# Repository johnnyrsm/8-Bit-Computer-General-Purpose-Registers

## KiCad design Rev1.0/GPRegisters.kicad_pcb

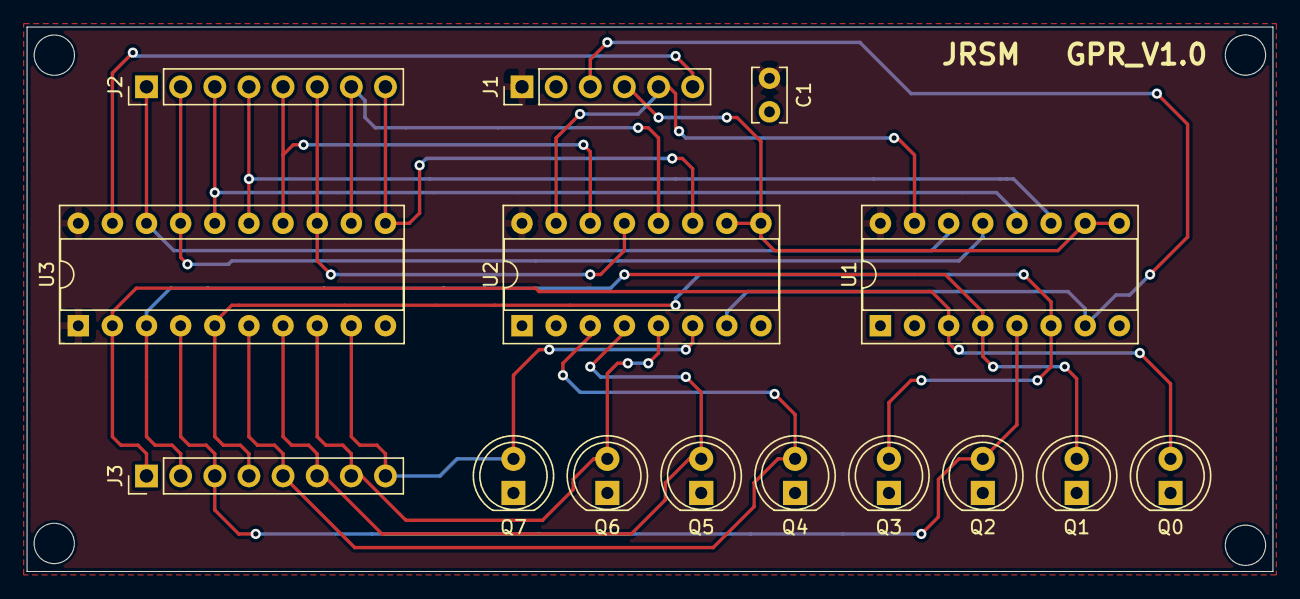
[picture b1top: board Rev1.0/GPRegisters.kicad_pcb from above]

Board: 2 copper layers, 92.7 x 40.5 mm, 15 parts (0 on the bottom side), 22 nets.

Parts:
C1: 1uF; C_Rect_L4.0mm_W2.5mm_P2.50mm
J1: Conn_01x06; Pin_Header_Straight_1x06_Pitch2.54mm
J2, J3: Conn_01x08; Pin_Header_Straight_1x08_Pitch2.54mm
Q0, Q1, Q2, Q3, Q4, Q5, Q6, Q7: LED; LED_D5.0mm
U1, U2: 74LS173; DIP-16_W7.62mm_Socket
U3: 74LS245; DIP-20_W7.62mm_Socket

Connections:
/CLK: J1.3, U1.7, U2.7
/CLR: J1.5, U1.15, U2.15
/D0: J2.1, U1.14, U3.18
/D1: J2.2, U1.13, U3.17
/D2: J2.3, U1.12, U3.16
/D3: J2.4, U1.11, U3.15
/D4: J2.5, U2.14, U3.14
/D5: J2.6, U2.13, U3.13
/D6: J2.7, U2.12, U3.12
/D7: J2.8, U2.11, U3.11
/Q0: J3.1, Q0.2, U1.3, U3.2
/Q1: J3.2, Q1.2, U1.4, U3.3
/Q2: J3.3, Q2.2, U1.5, U3.4
/Q3: J3.4, Q3.2, U1.6, U3.5
/Q4: J3.5, Q4.2, U2.3, U3.6
/Q5: J3.6, Q5.2, U2.4, U3.7
/Q6: J3.7, Q6.2, U2.5, U3.8
/Q7: J3.8, Q7.2, U2.6, U3.9
/~EN: J1.6, U3.19
/~LOAD: J1.4, U1.9, U1.10, U2.9, U2.10
GND: C1.2, J1.2, Q0.1, Q1.1, Q2.1, Q3.1, Q4.1, Q5.1, Q6.1, Q7.1, U1.1, U1.2, U1.8, U2.1, U2.2, U2.8, U3.10
VCC: C1.1, J1.1, U1.16, U2.16, U3.1, U3.20

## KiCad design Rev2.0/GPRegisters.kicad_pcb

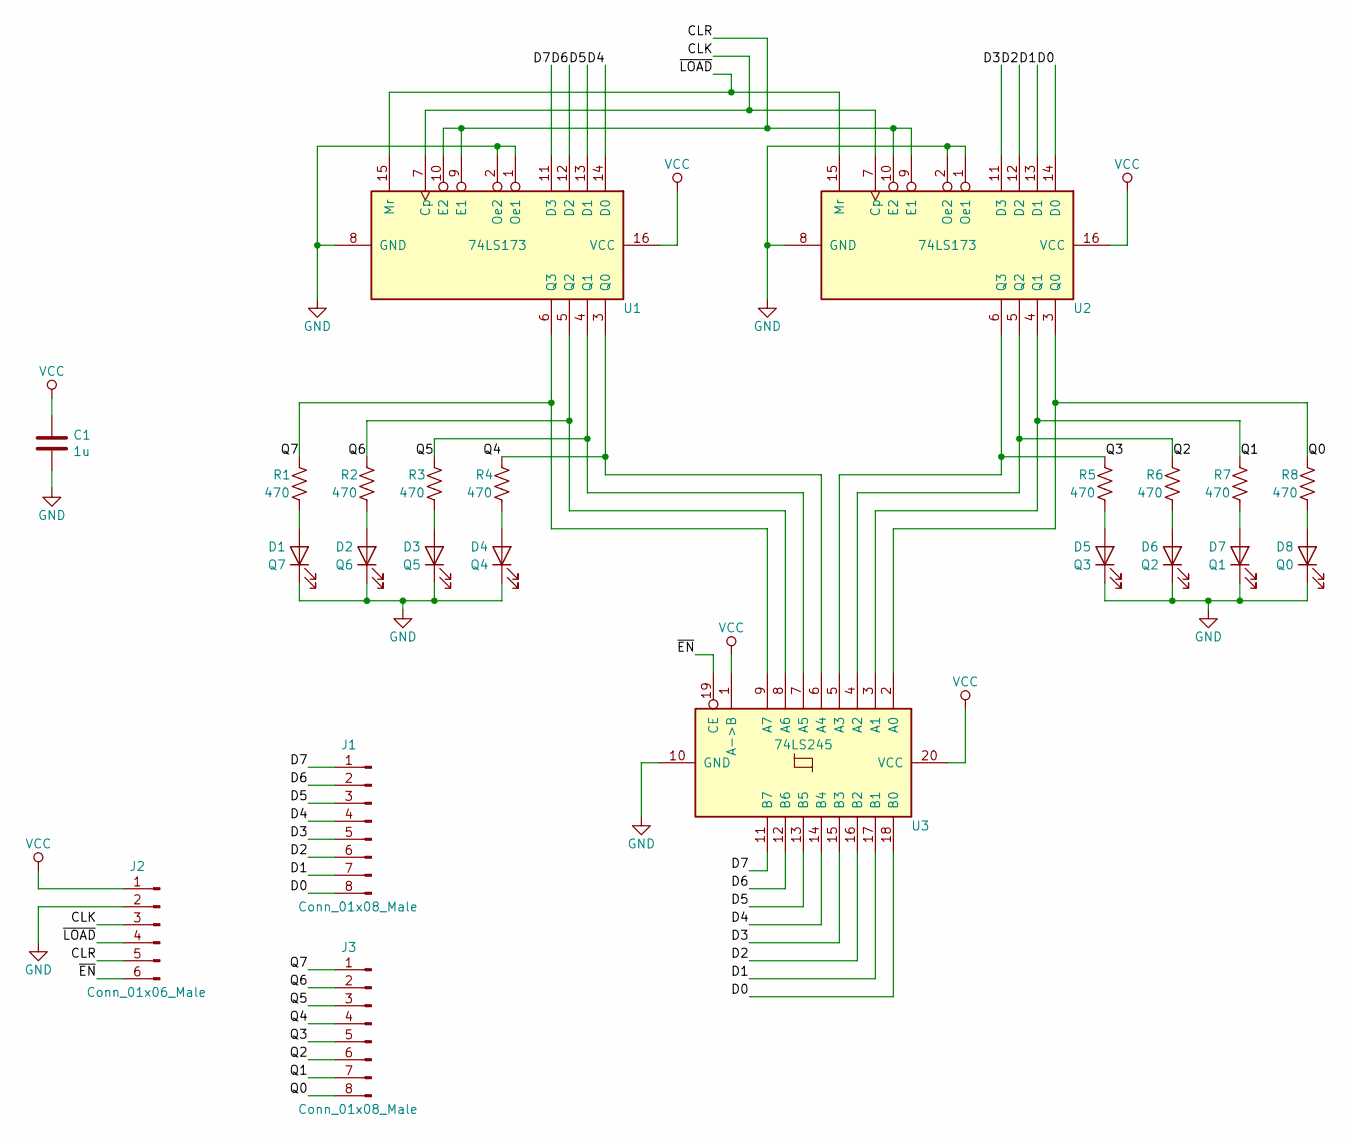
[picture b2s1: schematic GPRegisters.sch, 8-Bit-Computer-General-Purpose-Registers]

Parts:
C1: 1u; C_Rect_L4.0mm_W2.5mm_P2.50mm
D1: Q7; LED_D3.0mm
D2: Q6; LED_D3.0mm
D3: Q5; LED_D3.0mm
D4: Q4; LED_D3.0mm
D5: Q3; LED_D3.0mm
D6: Q2; LED_D3.0mm
D7: Q1; LED_D3.0mm
D8: Q0; LED_D3.0mm
J1, J3: Conn_01x08_Male; Pin_Header_Straight_1x08_Pitch2.54mm
J2: Conn_01x06_Male; Pin_Header_Straight_1x06_Pitch2.54mm
R1, R2, R3, R4, R5, R6, R7, R8: 470; R_Axial_DIN0207_L6.3mm_D2.5mm_P7.62mm_Horizontal
U1, U2: 74LS173; DIP-16_W7.62mm_Socket
U3: 74LS245; DIP-20_W7.62mm_Socket

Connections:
/CLK: J2.3, U1.7 (Cp), U2.7 (Cp)
/CLR: J2.5, U1.9 (E1), U1.10 (E2), U2.9 (E1), U2.10 (E2)
/D0: J1.8, U2.14 (D0), U3.18 (B0)
/D1: J1.7, U2.13 (D1), U3.17 (B1)
/D2: J1.6, U2.12 (D2), U3.16 (B2)
/D3: J1.5, U2.11 (D3), U3.15 (B3)
/D4: J1.4, U1.14 (D0), U3.14 (B4)
/D5: J1.3, U1.13 (D1), U3.13 (B5)
/D6: J1.2, U1.12 (D2), U3.12 (B6)
/D7: J1.1, U1.11 (D3), U3.11 (B7)
/Q0: J3.8, R8.1, U2.3 (Q0), U3.2 (A0)
/Q1: J3.7, R7.1, U2.4 (Q1), U3.3 (A1)
/Q2: J3.6, R6.1, U2.5 (Q2), U3.4 (A2)
/Q3: J3.5, R5.1, U2.6 (Q3), U3.5 (A3)
/Q4: J3.4, R4.1, U1.3 (Q0), U3.6 (A4)
/Q5: J3.3, R3.1, U1.4 (Q1), U3.7 (A5)
/Q6: J3.2, R2.1, U1.5 (Q2), U3.8 (A6)
/Q7: J3.1, R1.1, U1.6 (Q3), U3.9 (A7)
/~EN: J2.6, U3.19 (CE)
/~LOAD: J2.4, U1.15 (Mr), U2.15 (Mr)
GND: C1.2, D1.1 (K), D2.1 (K), D3.1 (K), D4.1 (K), D5.1 (K), D6.1 (K), D7.1 (K), D8.1 (K), J2.2, U1.1 (Oe1), U1.2 (Oe2), U1.8 (GND), U2.1 (Oe1), U2.2 (Oe2), U2.8 (GND), U3.10 (GND)
unnamed: D1.2 (A), R1.2
unnamed: D2.2 (A), R2.2
unnamed: D3.2 (A), R3.2
unnamed: D4.2 (A), R4.2
unnamed: D5.2 (A), R5.2
unnamed: D6.2 (A), R6.2
unnamed: D7.2 (A), R7.2
unnamed: D8.2 (A), R8.2
VCC: C1.1, J2.1, U1.16 (VCC), U2.16 (VCC), U3.1 (A->B), U3.20 (VCC)

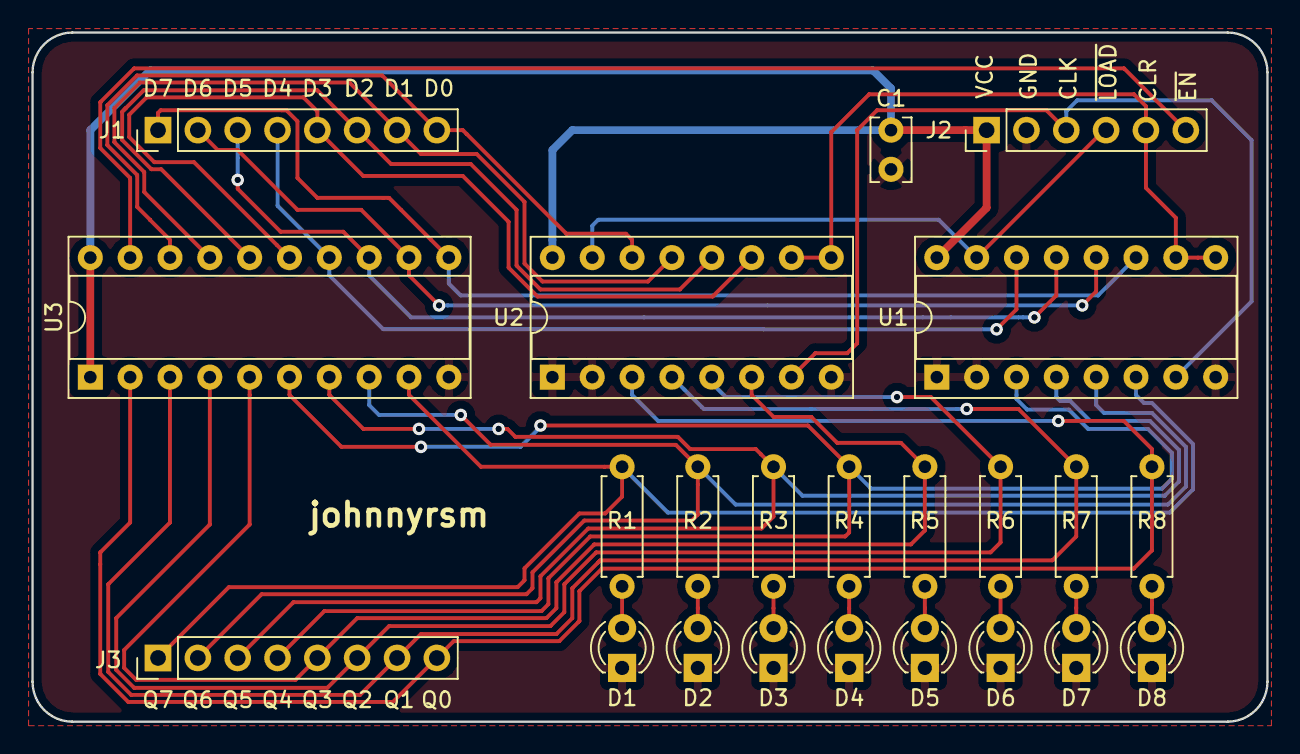
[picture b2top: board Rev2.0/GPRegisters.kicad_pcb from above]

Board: 2 copper layers, 78.7 x 43.9 mm, 23 parts (0 on the bottom side), 30 nets.

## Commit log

2020-01-14 Initial commit - Kicad Layout Files
